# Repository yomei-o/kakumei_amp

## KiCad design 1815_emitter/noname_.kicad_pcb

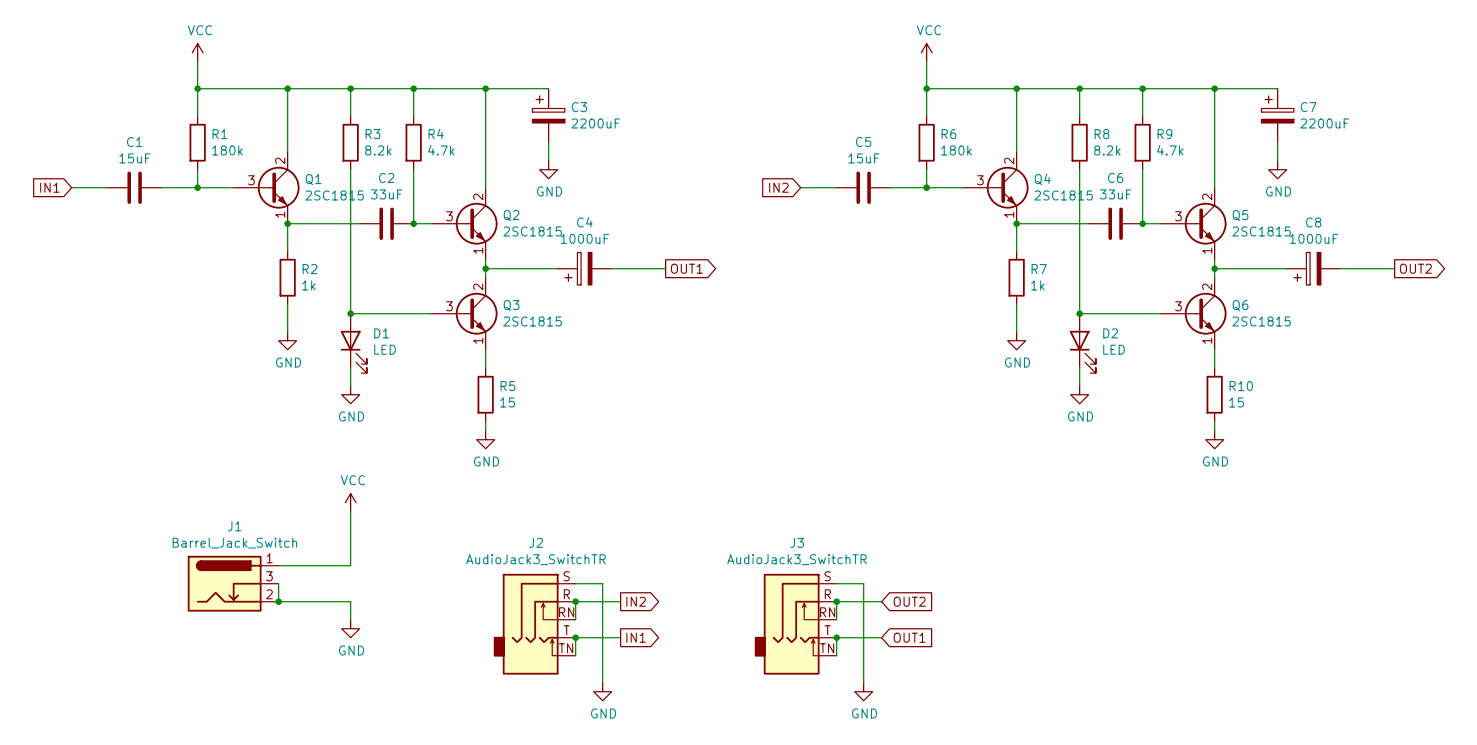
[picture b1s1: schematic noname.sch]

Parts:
C1, C5: 15uF; C_Disc_D5.0mm_W2.5mm_P2.50mm
C2, C6: 33uF; CP_Radial_D8.0mm_P5.00mm
C3, C7: 2200uF; CP_Radial_D10.0mm_P5.00mm
C4, C8: 1000uF; CP_Radial_D10.0mm_P5.00mm
D1, D2: LED; LED_D3.0mm
J1: Barrel_Jack_Switch; BarrelJack_Horizontal
J2, J3: AudioJack3_SwitchTR; Jack_3.5mm_Ledino_KB3SPRS_Horizontal
Q1, Q2, Q3, Q4, Q5, Q6: 2SC1815; TO-92_Inline
R1, R6: 180k; R_Axial_DIN0207_L6.3mm_D2.5mm_P10.16mm_Horizontal
R2, R7: 1k; R_Axial_DIN0207_L6.3mm_D2.5mm_P10.16mm_Horizontal
R3, R8: 8.2k; R_Axial_DIN0207_L6.3mm_D2.5mm_P10.16mm_Horizontal
R4, R9: 4.7k; R_Axial_DIN0207_L6.3mm_D2.5mm_P10.16mm_Horizontal
R5, R10: 15; R_Axial_DIN0207_L6.3mm_D2.5mm_P10.16mm_Horizontal

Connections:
GND: C3.2, C7.2, D1.1 (K), D2.1 (K), J1.2, J1.3, J2.S, J3.S, R2.2, R5.2, R7.2, R10.2
IN1: C1.2, J2.T, J2.TN
IN2: C5.2, J2.R, J2.RN
unnamed: C1.1, Q1.3 (B), R1.2
unnamed: C2.1, Q2.3 (B), R4.2
unnamed: C2.2, Q1.1 (E), R2.1
unnamed: C4.1, Q2.1 (E), Q3.2 (C)
unnamed: C5.1, Q4.3 (B), R6.2
unnamed: C6.1, Q5.3 (B), R9.2
unnamed: C6.2, Q4.1 (E), R7.1
unnamed: C8.1, Q5.1 (E), Q6.2 (C)
unnamed: D1.2 (A), Q3.3 (B), R3.2
unnamed: D2.2 (A), Q6.3 (B), R8.2
unnamed: Q3.1 (E), R5.1
unnamed: Q6.1 (E), R10.1
OUT1: C4.2, J3.T, J3.TN
OUT2: C8.2, J3.R, J3.RN
VCC: C3.1, C7.1, J1.1, Q1.2 (C), Q2.2 (C), Q4.2 (C), Q5.2 (C), R1.1, R3.1, R4.1, R6.1, R8.1, R9.1

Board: 2 copper layers, 29 parts (0 on the bottom side), 18 nets, no tracks yet.

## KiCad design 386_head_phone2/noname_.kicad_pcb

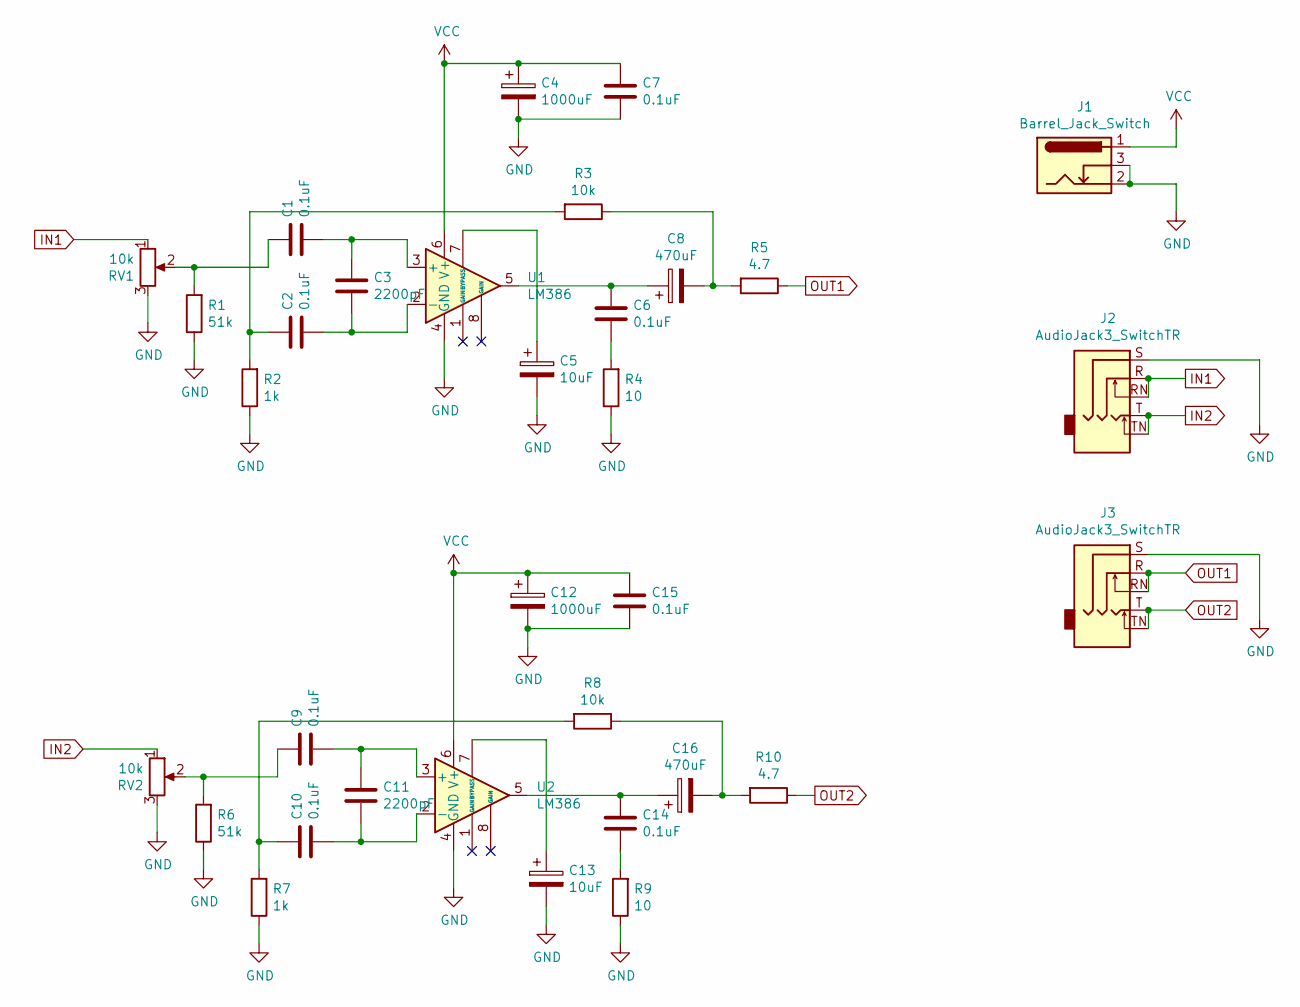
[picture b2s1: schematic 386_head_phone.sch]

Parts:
C1, C2, C6, C7, C9, C10, C14, C15: 0.1uF; C_Disc_D4.3mm_W1.9mm_P5.00mm
C3, C11: 2200pF; C_Disc_D3.0mm_W1.6mm_P2.50mm
C4, C12: 1000uF; CP_Radial_D10.0mm_P5.00mm
C5, C13: 10uF; CP_Radial_D5.0mm_P2.50mm
C8, C16: 470uF; CP_Radial_D10.0mm_P5.00mm
J1: Barrel_Jack_Switch; BarrelJack_Horizontal
J2, J3: AudioJack3_SwitchTR; Jack_3.5mm_Ledino_KB3SPRS_Horizontal
R1, R6: 51k; R_Axial_DIN0204_L3.6mm_D1.6mm_P7.62mm_Horizontal
R2, R7: 1k; R_Axial_DIN0204_L3.6mm_D1.6mm_P7.62mm_Horizontal
R3, R8: 10k; R_Axial_DIN0204_L3.6mm_D1.6mm_P7.62mm_Horizontal
R4, R9: 10; R_Axial_DIN0204_L3.6mm_D1.6mm_P7.62mm_Horizontal
R5, R10: 4.7; R_Axial_DIN0204_L3.6mm_D1.6mm_P7.62mm_Horizontal
RV1, RV2: 10k; PinHeader_1x03_P2.54mm_Vertical
U1, U2: LM386; DIP-8_W7.62mm_Socket

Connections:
GND: C4.2, C5.2, C7.1, C12.2, C13.2, C15.1, J1.2, J1.3, J2.S, J3.S, R1.1, R2.1, R4.1, R6.1, R7.1, R9.1, RV1.3, RV2.3, U1.4 (GND), U2.4 (GND)
IN1: J2.R, J2.RN, RV1.1
IN2: J2.T, J2.TN, RV2.1
unnamed: C1.1, C3.2, U1.3 (+)
unnamed: C1.2, R1.2, RV1.2
unnamed: C2.1, C3.1, U1.2 (-)
unnamed: C2.2, R2.2, R3.2
unnamed: C5.1, U1.7 (BYPASS)
unnamed: C6.1, R4.2
unnamed: C6.2, C8.1, U1.5
unnamed: C8.2, R3.1, R5.2
unnamed: C9.2, R6.2, RV2.2
unnamed: C10.1, C11.1, U2.2 (-)
unnamed: C10.2, R7.2, R8.2
unnamed: C9.1, C11.2, U2.3 (+)
unnamed: C13.1, U2.7 (BYPASS)
unnamed: C14.1, R9.2
unnamed: C14.2, C16.1, U2.5
unnamed: C16.2, R8.1, R10.2
OUT1: J3.R, J3.RN, R5.1
OUT2: J3.T, J3.TN, R10.1
VCC: C4.1, C7.2, C12.1, C15.2, J1.1, U1.6 (V+), U2.6 (V+)

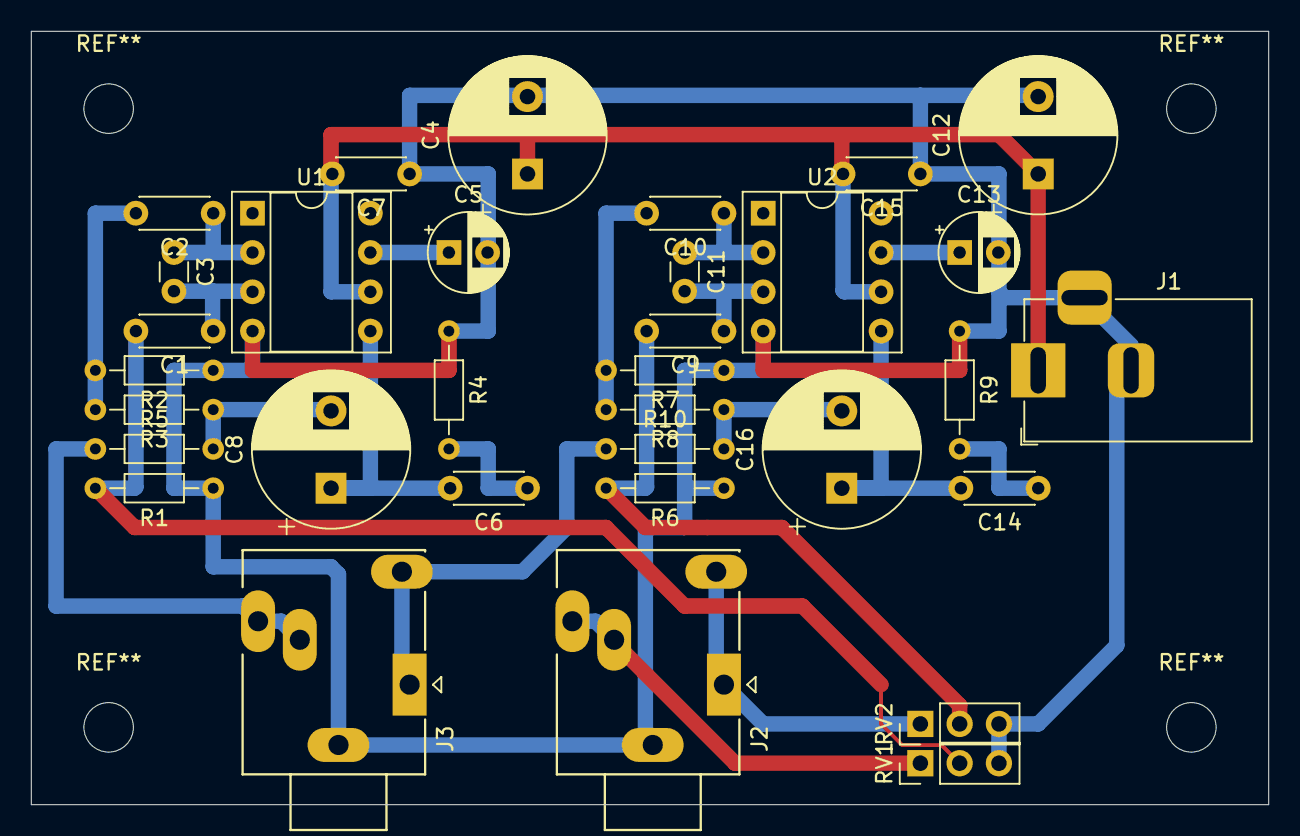
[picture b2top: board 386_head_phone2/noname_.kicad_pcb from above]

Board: 2 copper layers, 80.0 x 50.0 mm, 33 parts (0 on the bottom side), 22 nets.

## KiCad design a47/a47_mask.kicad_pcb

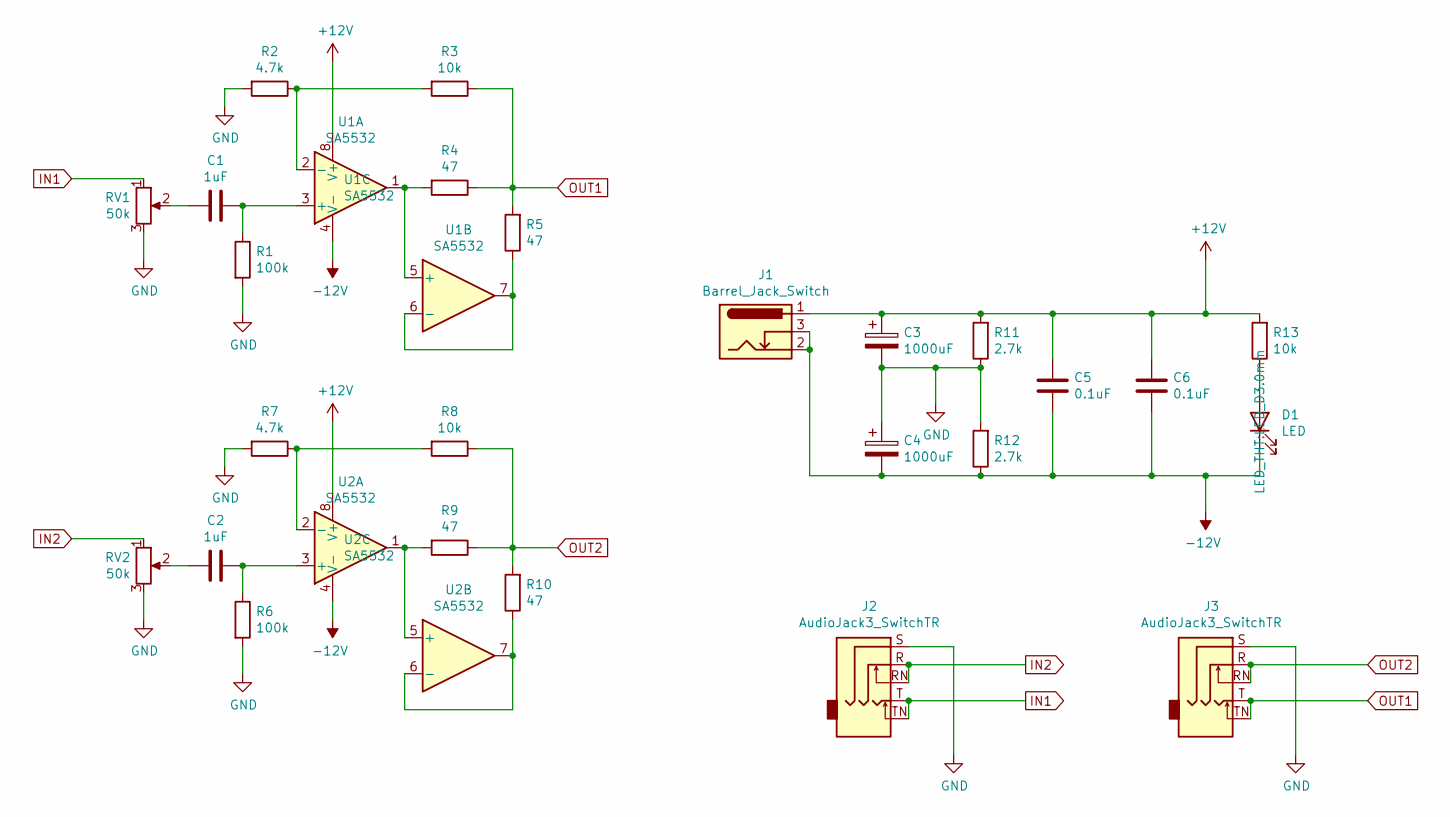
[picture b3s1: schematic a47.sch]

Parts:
C1, C2: 1uF; C_Disc_D10.5mm_W5.0mm_P5.00mm
C3, C4: 1000uF; CP_Radial_Tantal_D10.5mm_P5.00mm
C5, C6: 0.1uF; C_Disc_D7.5mm_W5.0mm_P5.00mm
D1: LED; LED_D3.0mm
J1: Barrel_Jack_Switch; BarrelJack_Horizontal
J2, J3: AudioJack3_SwitchTR; Jack_3.5mm_Ledino_KB3SPRS_Horizontal
R1, R6: 100k; R_Axial_DIN0207_L6.3mm_D2.5mm_P10.16mm_Horizontal
R2, R7: 4.7k; R_Axial_DIN0207_L6.3mm_D2.5mm_P10.16mm_Horizontal
R3, R8, R13: 10k; R_Axial_DIN0207_L6.3mm_D2.5mm_P10.16mm_Horizontal
R4, R5, R9, R10: 47; R_Axial_DIN0207_L6.3mm_D2.5mm_P10.16mm_Horizontal
R11, R12: 2.7k; R_Axial_DIN0207_L6.3mm_D2.5mm_P10.16mm_Horizontal
RV1, RV2: 50k; PinHeader_1x03_P2.54mm_Vertical
U1, U2: SA5532; DIP-8_W7.62mm

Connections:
+12V: C3.1, C5.2, C6.2, J1.1, R11.2, R13.2, U1.8 (V+), U2.8 (V+)
-12V: C4.2, C5.1, C6.1, D1.1 (K), J1.2, J1.3, R12.1, U1.4 (V-), U2.4 (V-)
GND: C3.2, C4.1, J2.S, J3.S, R1.2, R2.2, R6.2, R7.2, R11.1, R12.2, RV1.3, RV2.3
IN1: J2.T, J2.TN, RV1.1
IN2: J2.R, J2.RN, RV2.1
unnamed: C1.1, R1.1, U1.3 (+)
unnamed: C1.2, RV1.2
unnamed: C2.1, R6.1, U2.3 (+)
unnamed: C2.2, RV2.2
unnamed: D1.2 (A), R13.1
unnamed: R2.1, R3.2, U1.2 (-)
unnamed: R4.2, U1.1, U1.5 (+)
unnamed: R5.1, U1.6 (-), U1.7
unnamed: R7.1, R8.2, U2.2 (-)
unnamed: R9.2, U2.1, U2.5 (+)
unnamed: R10.1, U2.6 (-), U2.7
OUT1: J3.T, J3.TN, R3.1, R4.1, R5.2
OUT2: J3.R, J3.RN, R8.1, R9.1, R10.2

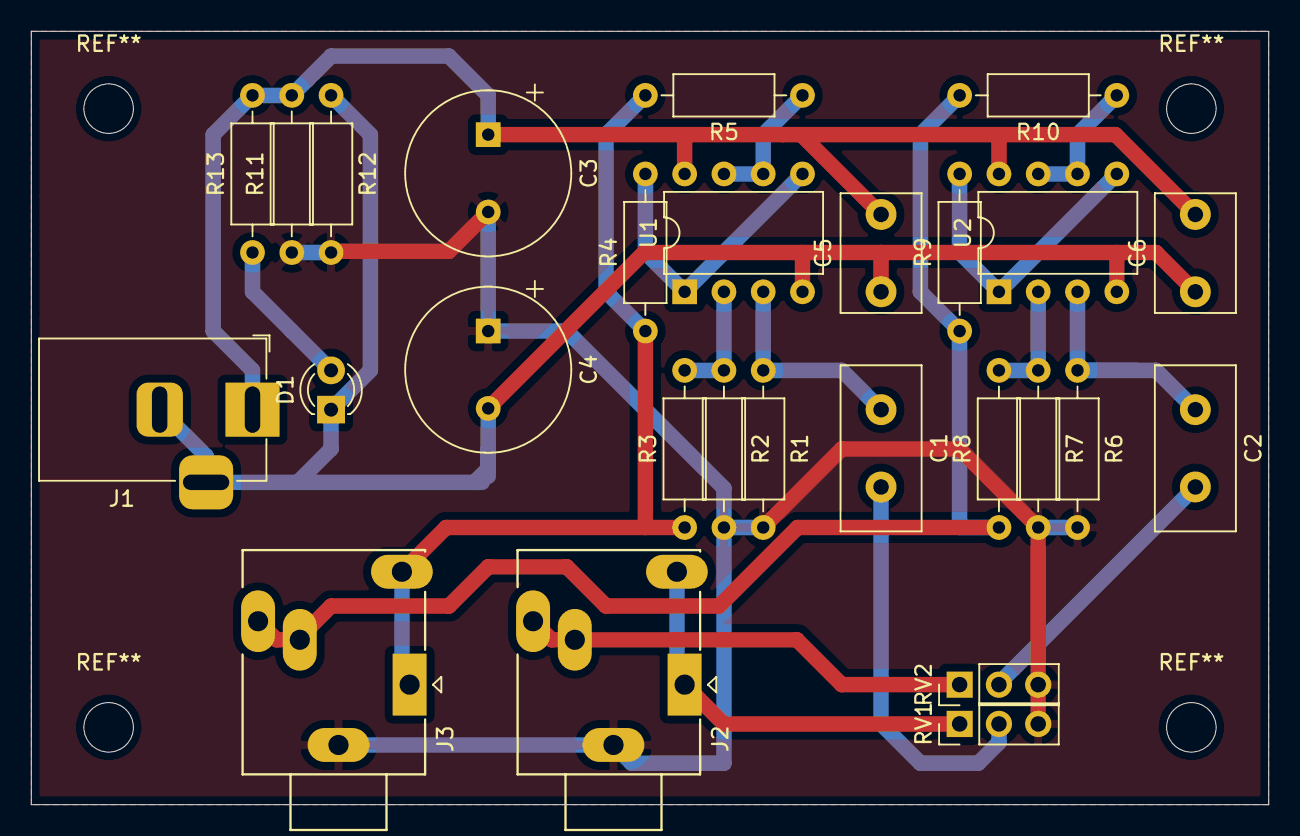
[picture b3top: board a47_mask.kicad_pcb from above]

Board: 2 copper layers, 80.0 x 50.0 mm, 27 parts (0 on the bottom side), 18 nets.

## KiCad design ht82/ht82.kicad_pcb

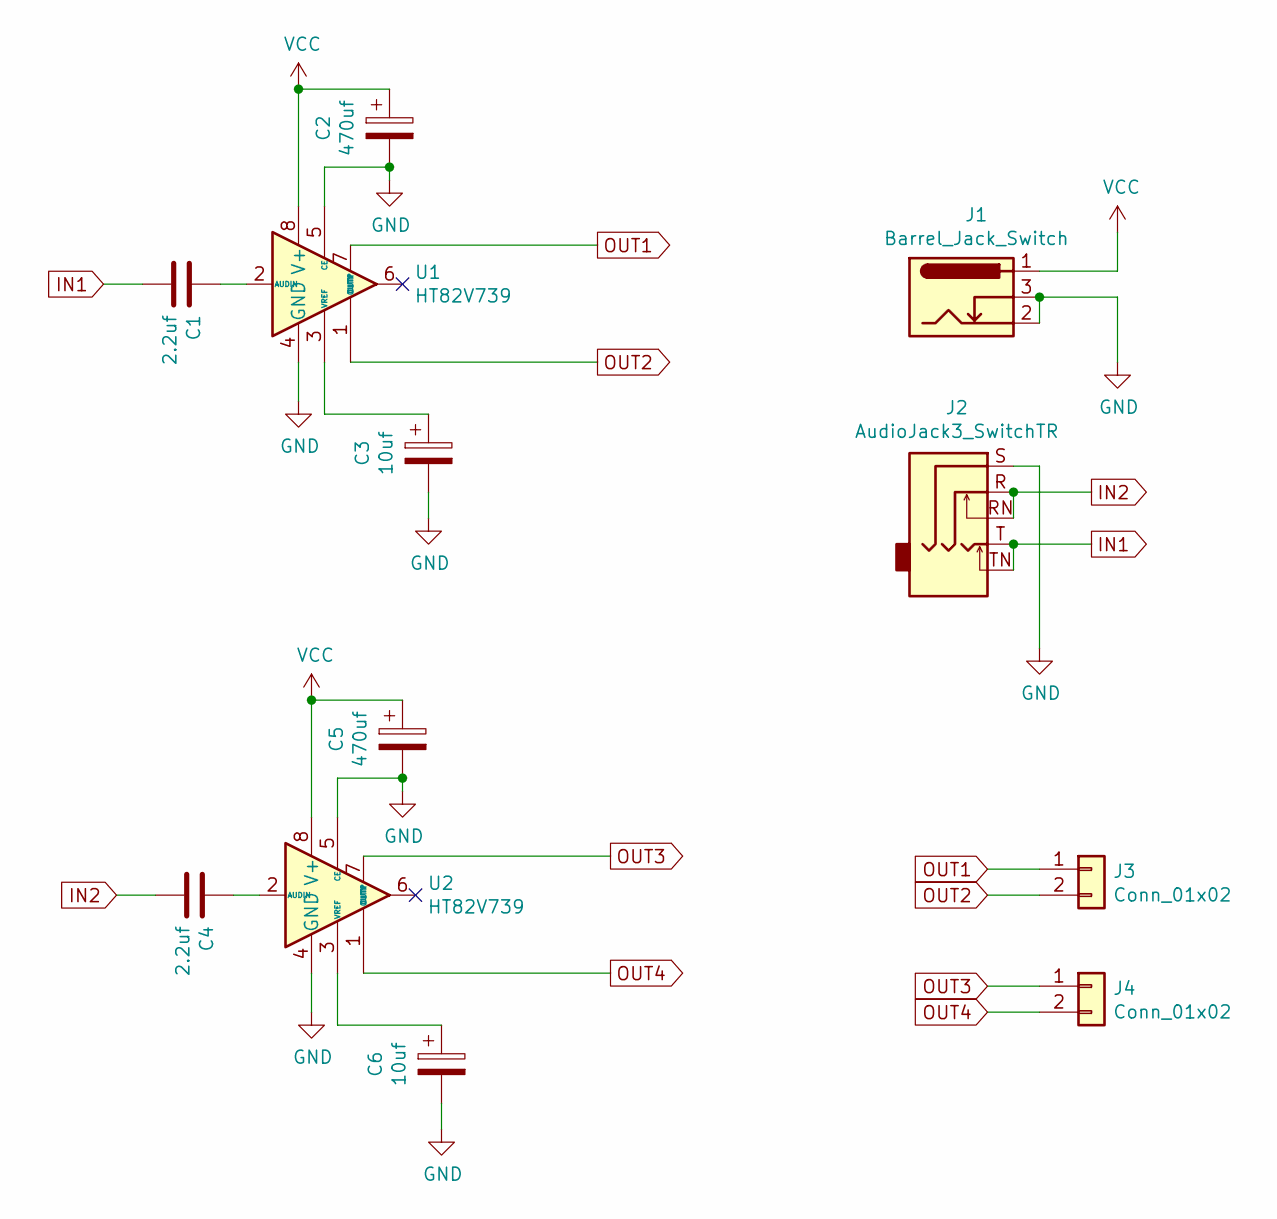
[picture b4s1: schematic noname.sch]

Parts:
C1, C4: 2.2uf; C_Rect_L10.3mm_W5.7mm_P7.50mm_MKS4
C2, C5: 470uf; CP_Radial_D8.0mm_P5.00mm
C3, C6: 10uf; CP_Radial_D5.0mm_P2.50mm
J1: Barrel_Jack_Switch; BarrelJack_Horizontal
J2: AudioJack3_SwitchTR; Jack_3.5mm_Ledino_KB3SPRS_Horizontal
J3, J4: Conn_01x02; TerminalBlock_bornier-2_P5.08mm
U1, U2: HT82V739; DIP-8_W7.62mm

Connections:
GND: C2.2, C3.2, C5.2, C6.2, J1.2, J1.3, J2.S, U1.4 (GND), U1.5 (CE), U2.4 (GND), U2.5 (CE)
IN1: C1.2, J2.T, J2.TN
IN2: C4.2, J2.R, J2.RN
unnamed: C1.1, U1.2 (AUDIN)
unnamed: C3.1, U1.3 (VREF)
unnamed: C4.1, U2.2 (AUDIN)
unnamed: C6.1, U2.3 (VREF)
OUT1: J3.1, U1.7 (OUTP)
OUT2: J3.2, U1.1 (OUTN)
OUT3: J4.1, U2.7 (OUTP)
OUT4: J4.2, U2.1 (OUTN)
VCC: C2.1, C5.1, J1.1, U1.8 (V+), U2.8 (V+)

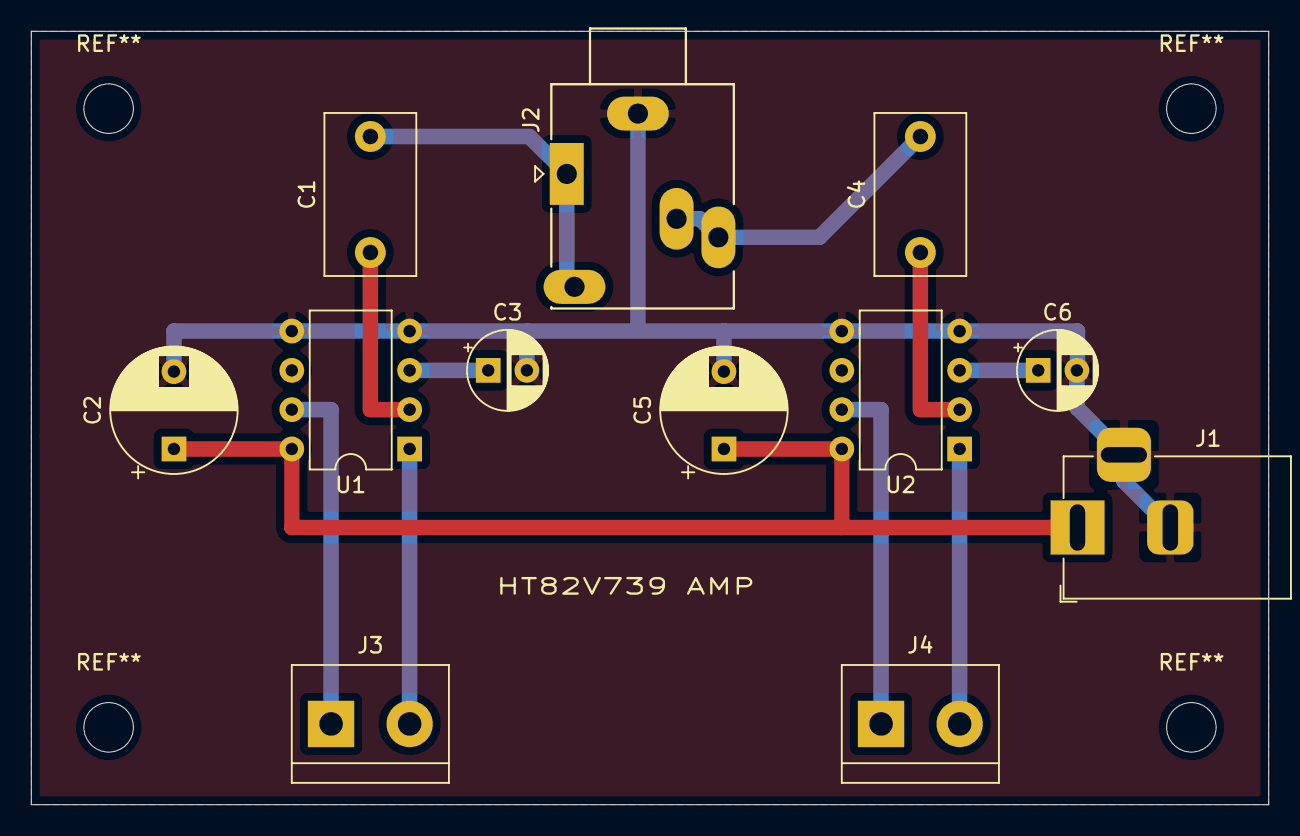
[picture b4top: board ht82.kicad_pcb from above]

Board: 2 copper layers, 80.0 x 50.0 mm, 12 parts (0 on the bottom side), 12 nets.

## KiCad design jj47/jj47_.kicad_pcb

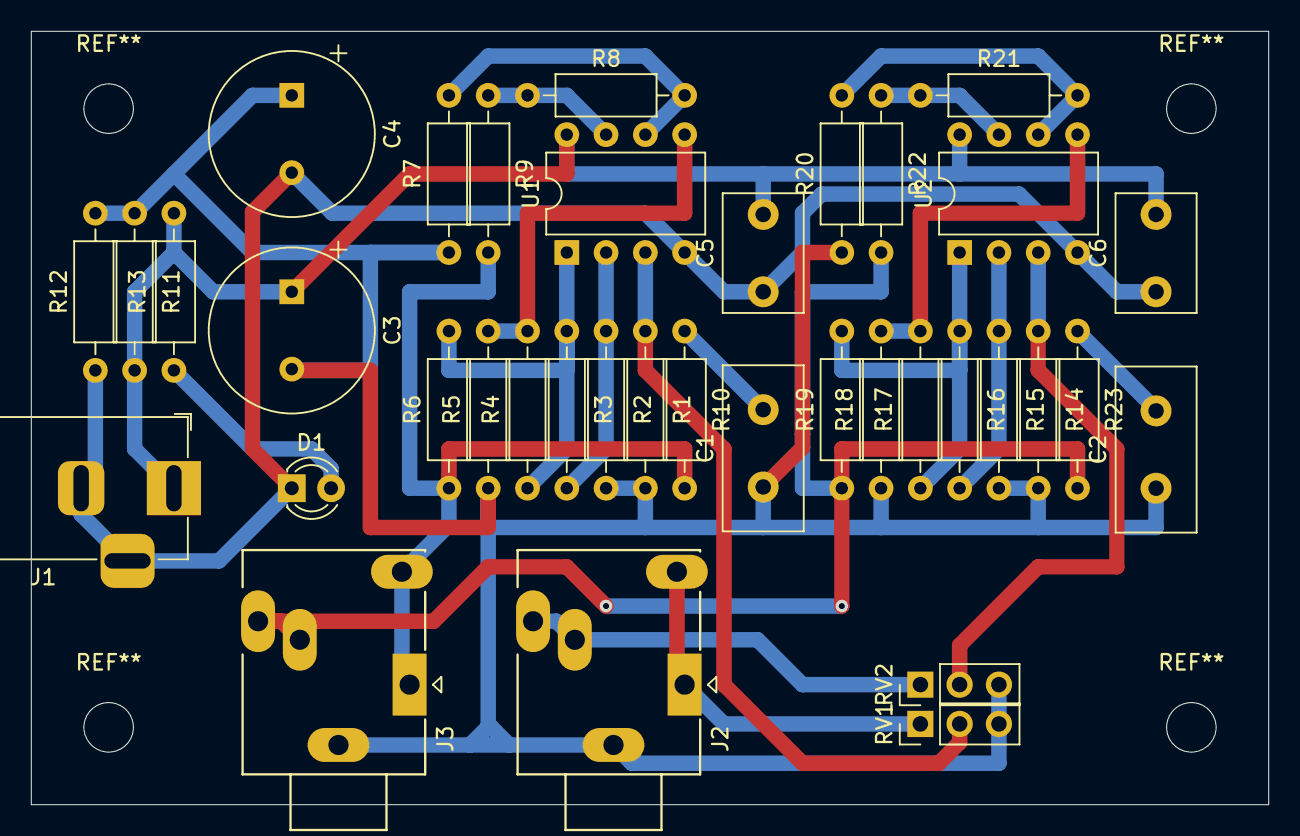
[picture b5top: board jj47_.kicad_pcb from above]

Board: 2 copper layers, 80.0 x 50.0 mm, 37 parts (0 on the bottom side), 22 nets.

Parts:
C1, C2: 0.1uF; C_Disc_D10.5mm_W5.0mm_P5.00mm
C3, C4: 1000uF; CP_Radial_Tantal_D10.5mm_P5.00mm
C5, C6: 0.1uF; C_Disc_D7.5mm_W5.0mm_P5.00mm
D1: LED; LED_D3.0mm
J1: Barrel_Jack_Switch; BarrelJack_Horizontal
J2, J3: AudioJack3_SwitchTR; Jack_3.5mm_Ledino_KB3SPRS_Horizontal
R1, R5, R14, R18: 110k; R_Axial_DIN0207_L6.3mm_D2.5mm_P10.16mm_Horizontal
R2, R7, R15, R20: 3.3k; R_Axial_DIN0207_L6.3mm_D2.5mm_P10.16mm_Horizontal
R3, R8, R13, R16, R21: 10k; R_Axial_DIN0207_L6.3mm_D2.5mm_P10.16mm_Horizontal
R4, R17: 330k; R_Axial_DIN0207_L6.3mm_D2.5mm_P10.16mm_Horizontal
R6, R9, R19, R22: 47; R_Axial_DIN0207_L6.3mm_D2.5mm_P10.16mm_Horizontal
R10, R23: 36; R_Axial_DIN0207_L6.3mm_D2.5mm_P10.16mm_Horizontal
R11, R12: 2.7k; R_Axial_DIN0207_L6.3mm_D2.5mm_P10.16mm_Horizontal
RV1, RV2: 10k; PinHeader_1x03_P2.54mm_Vertical
U1, U2: SA5532; DIP-8_W7.62mm

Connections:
+12V: C3.1, C5.2, C6.2, J1.1, R11.2, R13.2, U1.8, U2.8
-12V: C4.2, C5.1, C6.1, D1.1, J1.2, J1.3, R12.1, U1.4, U2.4
GND: C1.1, C2.1, C3.2, C4.1, J2.S, J3.S, R1.2, R2.2, R5.1, R7.1, R11.1, R12.2, R14.2, R15.2, R18.1, R20.1, RV1.3, RV2.3
IN1: J2.T, J2.TN, RV1.1
IN2: J2.R, J2.RN, RV2.1
unnamed: C1.2, R10.1
unnamed: C2.2, R23.1
unnamed: D1.2, R13.1
unnamed: R1.1, RV1.2, U1.3
unnamed: R2.1, R3.2, U1.2
unnamed: R3.1, R4.1, R6.2, U1.1
unnamed: R4.2, R5.2, U1.5
unnamed: R7.2, R8.2, U1.6
unnamed: R8.1, R9.1, U1.7
unnamed: R14.1, RV2.2, U2.3
unnamed: R15.1, R16.2, U2.2
unnamed: R16.1, R17.1, R19.2, U2.1
unnamed: R17.2, R18.2, U2.5
unnamed: R20.2, R21.2, U2.6
unnamed: R21.1, R22.1, U2.7
OUT1: J3.T, J3.TN, R6.1, R9.2, R10.2
OUT2: J3.R, J3.RN, R19.1, R22.2, R23.2

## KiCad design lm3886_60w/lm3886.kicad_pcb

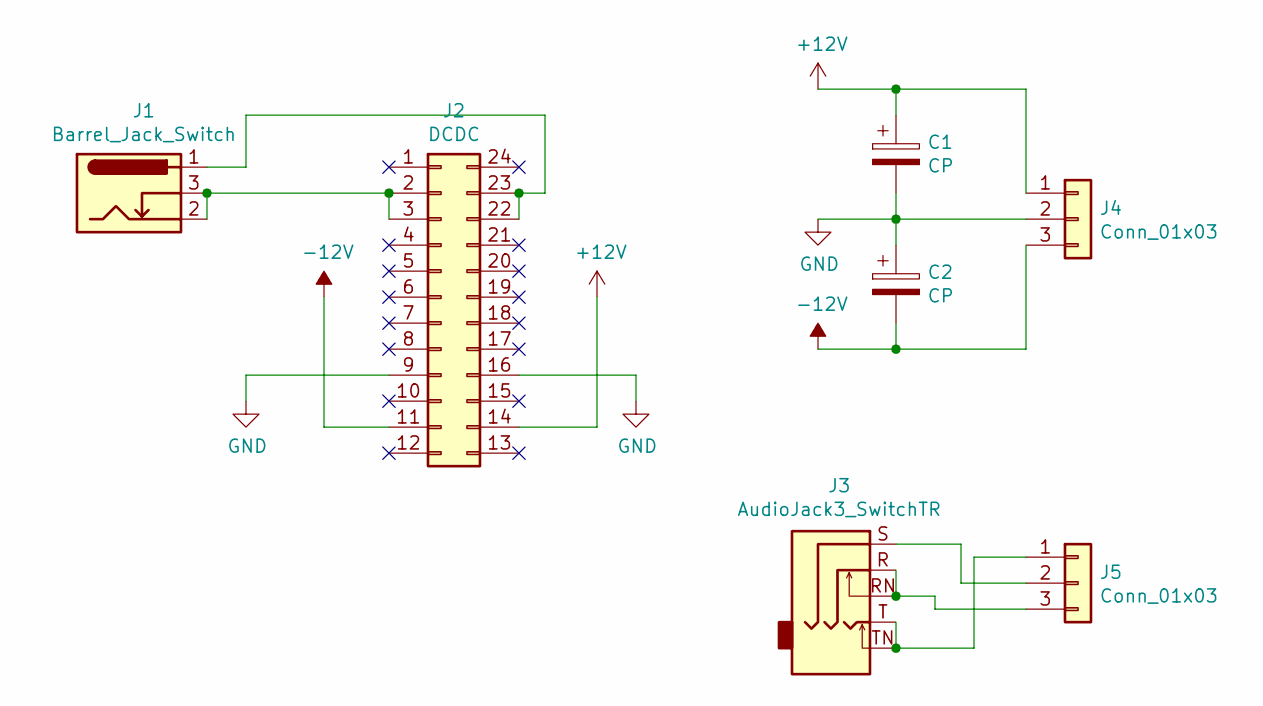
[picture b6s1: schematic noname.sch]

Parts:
C1, C2: CP; CP_Radial_D12.5mm_P5.00mm
J1: Barrel_Jack_Switch; BarrelJack_Horizontal
J2: DCDC; DIP-24_W15.24mm_Socket
J3: AudioJack3_SwitchTR; Jack_3.5mm_Ledino_KB3SPRS_Horizontal
J4, J5: Conn_01x03; TerminalBlock_bornier-3_P5.08mm

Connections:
+12V: C1.1, J2.14, J4.1
-12V: C2.2, J2.11, J4.3
GND: C1.2, C2.1, J2.9, J2.16, J4.2
unnamed: J1.1, J2.22, J2.23
unnamed: J1.2, J1.3, J2.2, J2.3
unnamed: J3.R, J3.RN, J5.3
unnamed: J3.S, J5.2
unnamed: J3.T, J3.TN, J5.1

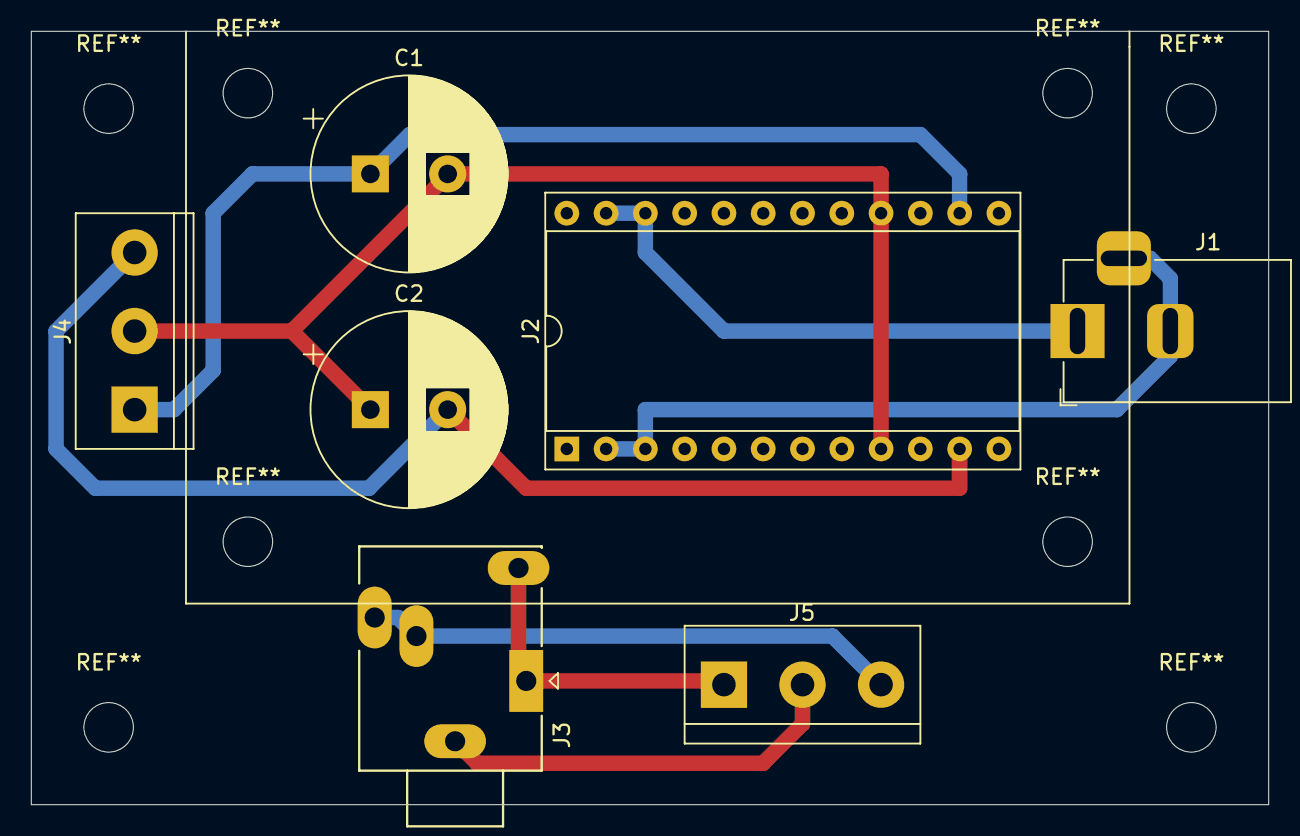
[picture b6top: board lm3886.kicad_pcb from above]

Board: 2 copper layers, 80.0 x 50.0 mm, 7 parts (0 on the bottom side), 8 nets.
